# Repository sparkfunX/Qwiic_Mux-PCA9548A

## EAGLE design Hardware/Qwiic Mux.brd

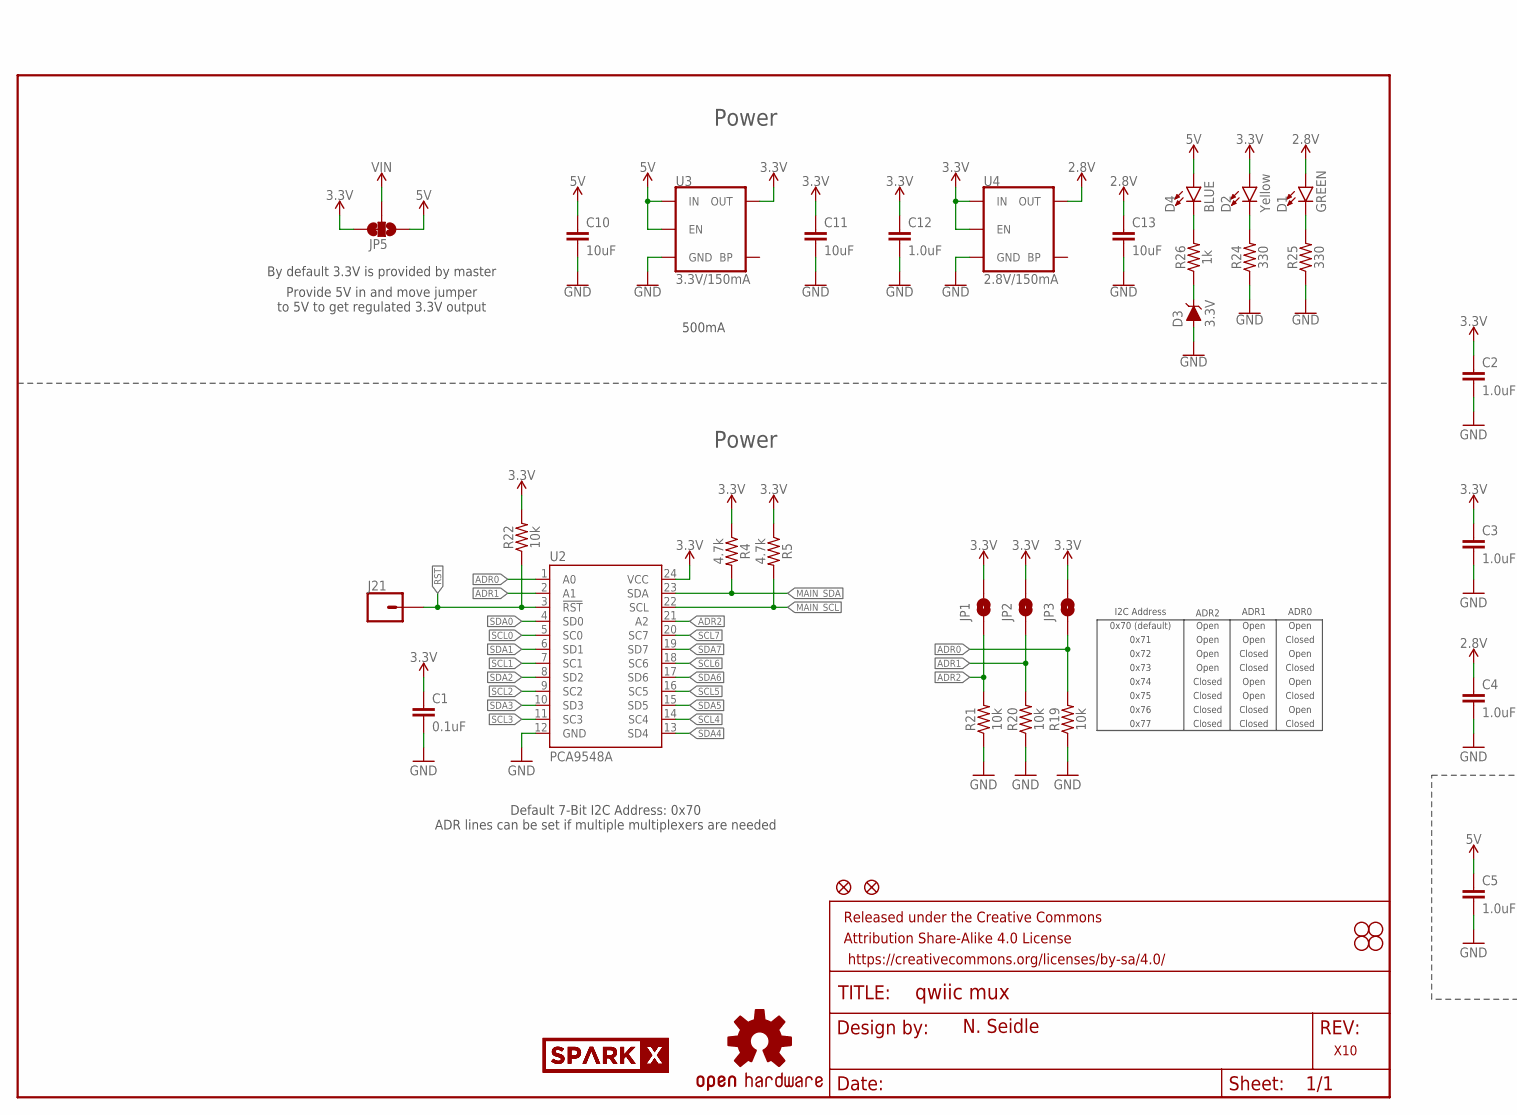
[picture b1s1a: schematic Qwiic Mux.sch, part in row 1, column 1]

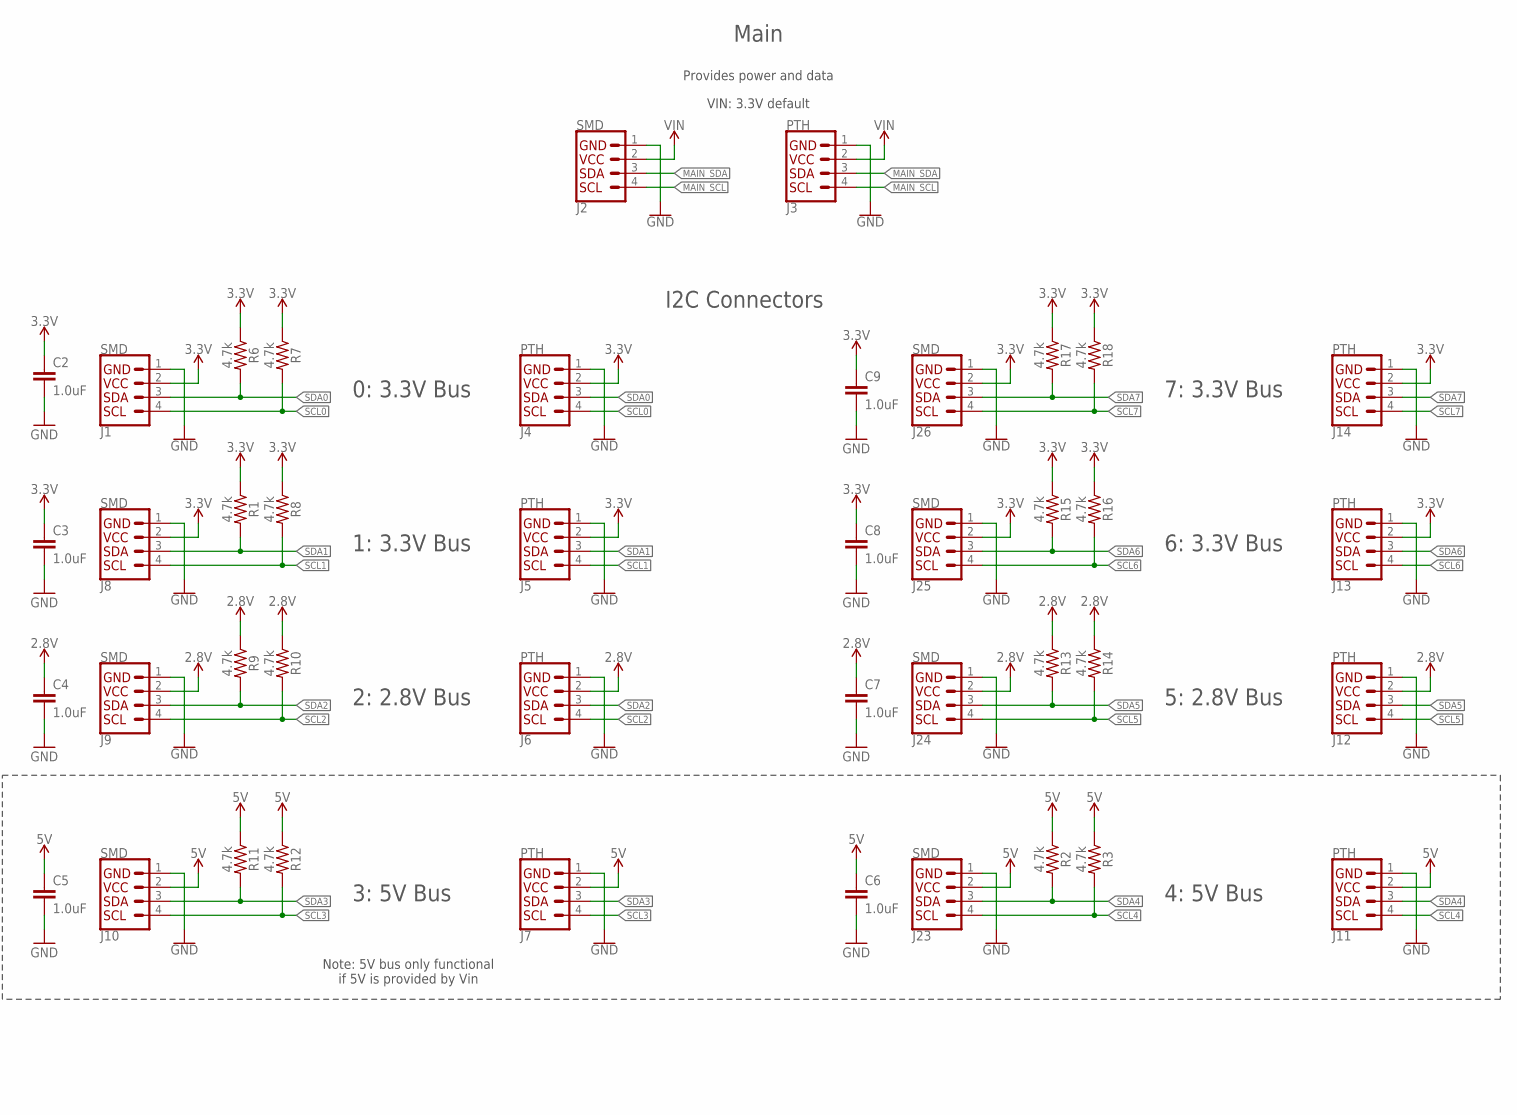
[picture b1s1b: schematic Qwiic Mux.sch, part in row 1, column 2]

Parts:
C1: 0.1uF; 0603
C2, C3, C4, C5, C6, C7, C8, C9, C12: 1.0uF; 0603
C10, C11, C13: 10uF; 0603
D1: GREEN; LED-0603
D2: Yellow; LED-0603
D3: 3.3V; SOD-323
D4: BLUE; LED-0603
FD1, FD2: FIDUCIAL1X2; FIDUCIAL-1X2
FRAME1: FRAME-LETTER; CREATIVE_COMMONS
H1, H2, H3, H4: STAND-OFF
J1, J2, J8, J9, J10, J23, J24, J25, J26: SMD; 1X04_1MM_RA
J3, J4, J5, J6, J7, J11, J12, J13, J14: PTH; 1X04_NO_SILK
J21: CONN_01PTH_NO_SILK_YES_STOP; 1X01_NO_SILK
JP1, JP2, JP3: JUMPER-SMT_2_NO_SILK; SMT-JUMPER_2_NO_SILK
JP5: JUMPER-SMT_3_1-NC_TRACE_SILK; SMT-JUMPER_3_1-NC_TRACE_SILK
LOGO1: OSHW-LOGOMINI; OSHW-LOGO-MINI
R1, R2, R3, R4, R5, R6, R7, R8, R9, R10, R11, R12, R13, R14, R15, R16, R17, R18: 4.7k; 0603
R19, R20, R21, R22: 10k; 0603
R24, R25: 330; 0603
R26: 1k; 0603
U2: PCA9548A; TSSOP28
U3: 3.3V/150mA; SOT23-5
U4: 2.8V/150mA; SOT23-5
U$1: SPARKX-LOGO3; SPARKX-SMALL
U$2: SPARKX-LOGO5; SPARKX-LARGE

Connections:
2.8V: C4.1, C7.1, C13.1, D1.A, J6.2 (VCC), J9.2 (VCC), J12.2 (VCC), J24.2 (VCC), R9.1, R10.1, R13.1, R14.1, U4.5 (OUT)
3.3V: C1.1, C2.1, C3.1, C8.1, C9.1, C11.1, C12.1, D2.A, J1.2 (VCC), J4.2 (VCC), J5.2 (VCC), J8.2 (VCC), J13.2 (VCC), J14.2 (VCC), J25.2 (VCC), J26.2 (VCC), JP1.2, JP2.2, JP3.2, JP5.3, R1.1, R4.1, R5.1, R6.1, R7.1, R8.1, R15.1, R16.1, R17.1, R18.1, R22.2, U2.24 (VCC), U3.5 (OUT), U4.1 (IN), U4.3 (EN)
5V: C5.1, C6.1, C10.1, D4.A, J7.2 (VCC), J10.2 (VCC), J11.2 (VCC), J23.2 (VCC), JP5.1, R2.1, R3.1, R11.1, R12.1, U3.1 (IN), U3.3 (EN)
!RST: J21.1, R22.1, U2.3 (!RST)
ADR0: JP3.1, R19.2, U2.1 (A0)
ADR1: JP2.1, R20.2, U2.2 (A1)
ADR2: JP1.1, R21.2, U2.21 (A2)
GND: C1.2, C2.2, C3.2, C4.2, C5.2, C6.2, C7.2, C8.2, C9.2, C10.2, C11.2, C12.2, C13.2, D3.A, J1.1 (GND), J2.1 (GND), J3.1 (GND), J4.1 (GND), J5.1 (GND), J6.1 (GND), J7.1 (GND), J8.1 (GND), J9.1 (GND), J10.1 (GND), J11.1 (GND), J12.1 (GND), J13.1 (GND), J14.1 (GND), J23.1 (GND), J24.1 (GND), J25.1 (GND), J26.1 (GND), R19.1, R20.1, R21.1, R24.1, R25.1, U2.12 (GND), U3.2 (GND), U4.2 (GND)
MAIN_SCL: J2.4 (SCL), J3.4 (SCL), R5.2, U2.22 (SCL)
MAIN_SDA: J2.3 (SDA), J3.3 (SDA), R4.2, U2.23 (SDA)
unnamed: D2.C, R24.2
unnamed: D3.C, R26.1
unnamed: D1.C, R25.2
unnamed: D4.C, R26.2
SCL0: J1.4 (SCL), J4.4 (SCL), R7.2, U2.5 (SC0)
SCL1: J5.4 (SCL), J8.4 (SCL), R8.2, U2.7 (SC1)
SCL2: J6.4 (SCL), J9.4 (SCL), R10.2, U2.9 (SC2)
SCL3: J7.4 (SCL), J10.4 (SCL), R12.2, U2.11 (SC3)
SCL4: J11.4 (SCL), J23.4 (SCL), R3.2, U2.14 (SC4)
SCL5: J12.4 (SCL), J24.4 (SCL), R14.2, U2.16 (SC5)
SCL6: J13.4 (SCL), J25.4 (SCL), R16.2, U2.18 (SC6)
SCL7: J14.4 (SCL), J26.4 (SCL), R18.2, U2.20 (SC7)
SDA0: J1.3 (SDA), J4.3 (SDA), R6.2, U2.4 (SD0)
SDA1: J5.3 (SDA), J8.3 (SDA), R1.2, U2.6 (SD1)
SDA2: J6.3 (SDA), J9.3 (SDA), R9.2, U2.8 (SD2)
SDA3: J7.3 (SDA), J10.3 (SDA), R11.2, U2.10 (SD3)
SDA4: J11.3 (SDA), J23.3 (SDA), R2.2, U2.13 (SD4)
SDA5: J12.3 (SDA), J24.3 (SDA), R13.2, U2.15 (SD5)
SDA6: J13.3 (SDA), J25.3 (SDA), R15.2, U2.17 (SD6)
SDA7: J14.3 (SDA), J26.3 (SDA), R17.2, U2.19 (SD7)
VIN: J2.2 (VCC), J3.2 (VCC), JP5.2

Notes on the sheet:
N. Seidle
X10
I2C Connectors
Default 7-Bit I2C Address: 0x70 ADR lines can be set if multiple multiplexers are needed
Main
0: 3.3V Bus
1: 3.3V Bus
2: 2.8V Bus
3: 5V Bus
4: 5V Bus
5: 2.8V Bus
6: 3.3V Bus
7: 3.3V Bus
Power
By default 3.3V is provided by master
Provides power and data
Provide 5V in and move jumper to 5V to get regulated 3.3V output
VIN: 3.3V default
Note: 5V bus only functional if 5V is provided by Vin
500mA
I2C Address
ADR0
ADR1
ADR2
Open
Closed
0x70 (default)
0x71
0x72
0x73
0x74
0x75
0x76
0x77

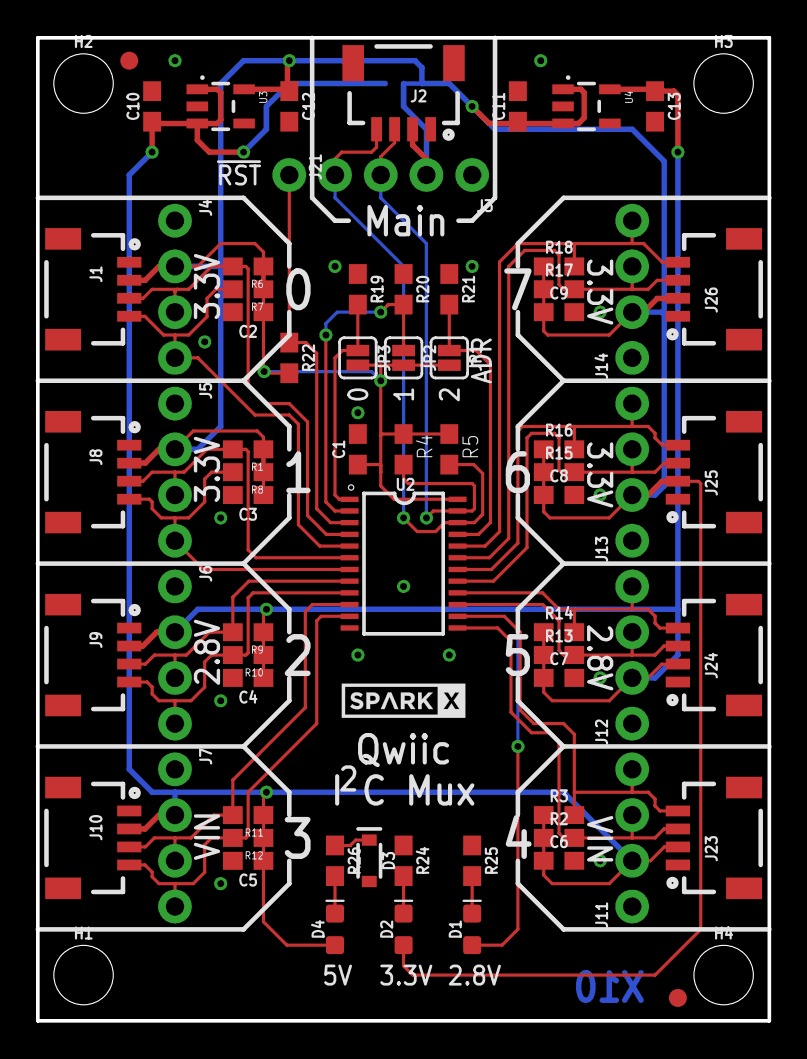
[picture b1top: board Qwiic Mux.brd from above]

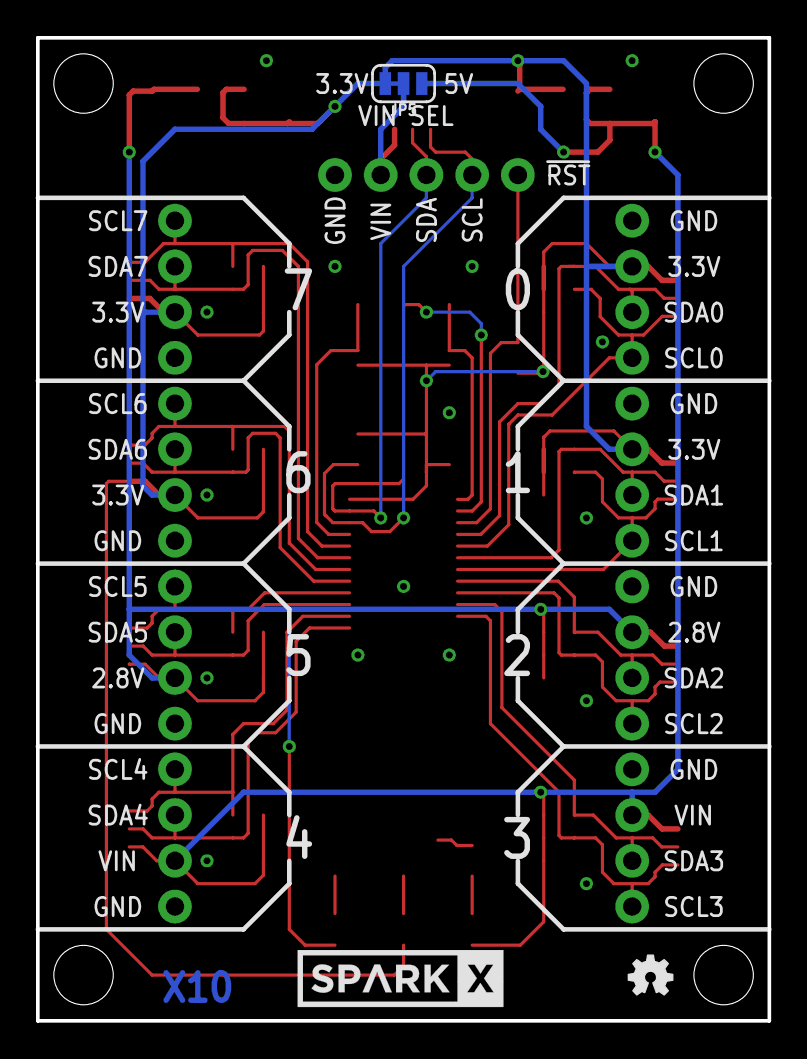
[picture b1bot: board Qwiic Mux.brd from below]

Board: 2 copper layers, 40.6 x 54.6 mm, 78 parts (3 on the bottom side), 31 nets.

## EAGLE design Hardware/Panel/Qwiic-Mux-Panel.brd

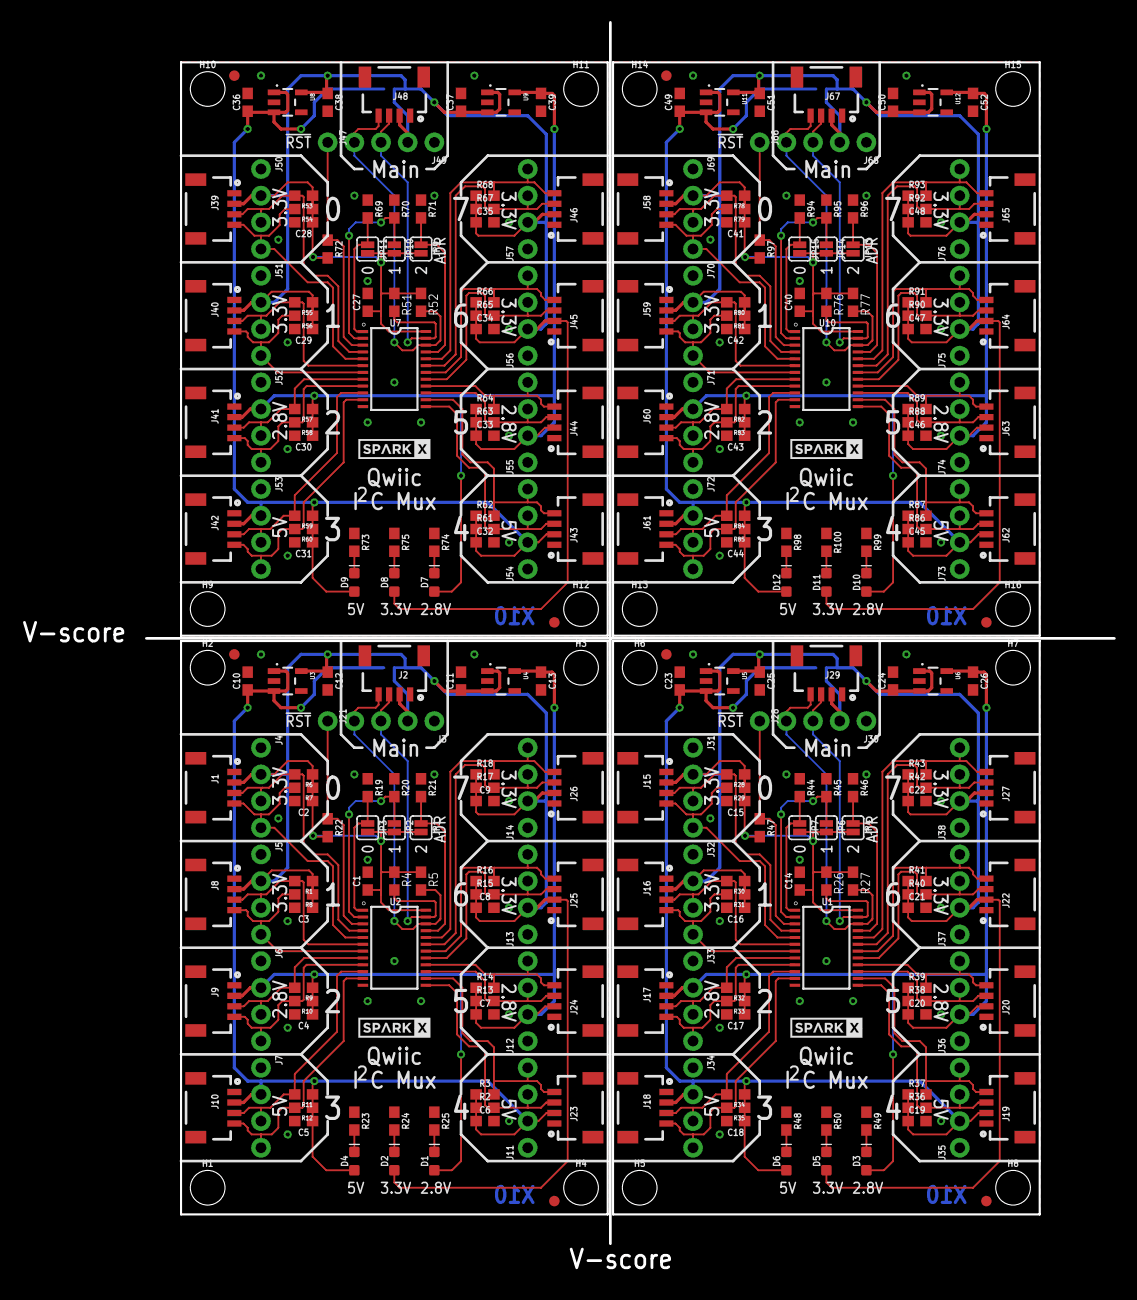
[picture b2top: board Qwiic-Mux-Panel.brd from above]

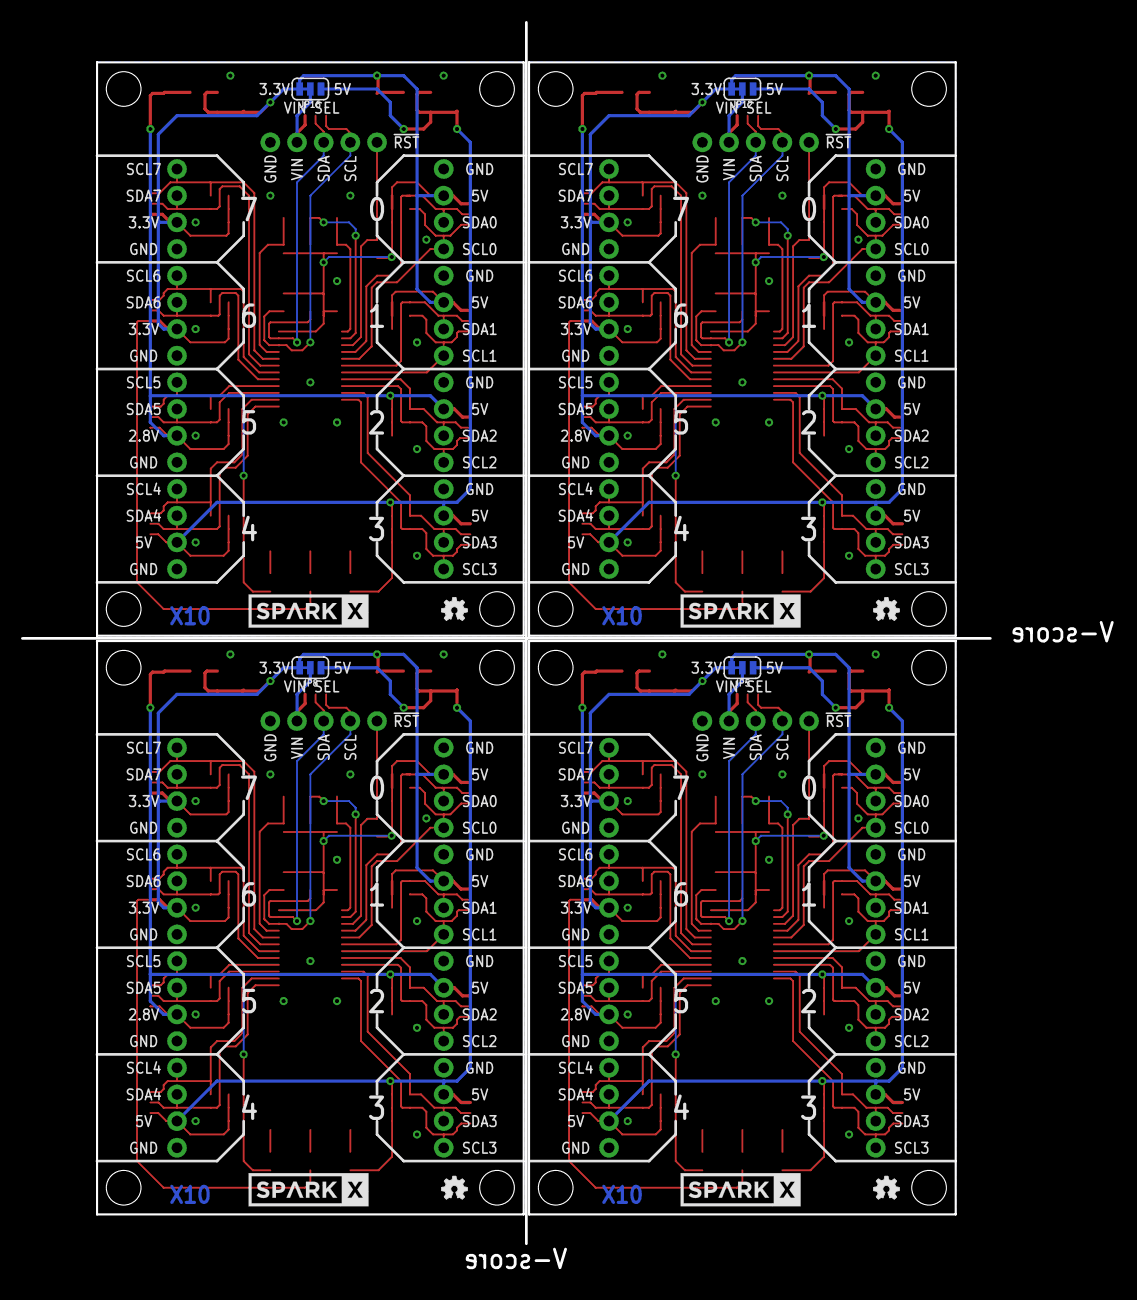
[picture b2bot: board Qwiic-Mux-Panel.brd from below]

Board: 2 copper layers, 104.0 x 119.6 mm, 304 parts (12 on the bottom side), 120 nets.

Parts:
C1, C14, C27, C40: 0.1uF; 0603
C2, C3, C4, C5, C6, C7, C8, C9, C12, C15, C16, C17, C18, C19, C20, C21, C22, C25, C28, C29, C30, C31, C32, C33, C34, C35, C38, C41, C42, C43, C44, C45, C46, C47, C48, C51: 1.0uF; 0603
C10, C11, C13, C23, C24, C26, C36, C37, C39, C49, C50, C52: 10uF; 0603
D1, D3, D7, D10: GREEN; LED-0603
D2, D5, D8, D11: Yellow; LED-0603
D4, D6, D9, D12: BLUE; LED-0603
FD1, FD2, FD3, FD4, FD5, FD6, FD7, FD8: FIDUCIAL1X2; FIDUCIAL-1X2
H1, H2, H3, H4, H5, H6, H7, H8, H9, H10, H11, H12, H13, H14, H15, H16: STAND-OFF
J1, J2, J8, J9, J10, J15, J16, J17, J18, J19, J20, J22, J23, J24, J25, J26, J27, J29, J39, J40, J41, J42, J43, J44, J45, J46, J48, J58, J59, J60, J61, J62, J63, J64, J65, J67: SMD; 1X04_1MM_RA
J3, J4, J5, J6, J7, J11, J12, J13, J14, J30, J31, J32, J33, J34, J35, J36, J37, J38, J49, J50, J51, J52, J53, J54, J55, J56, J57, J68, J69, J70, J71, J72, J73, J74, J75, J76: PTH; 1X04_NO_SILK
J21, J28, J47, J66: 1X01_NO_SILK
JP1, JP2, JP3, JP4, JP6, JP7, JP9, JP10, JP11, JP13, JP14, JP15: SMT-JUMPER_2_NO_SILK
JP5, JP8, JP12, JP16: SMT-JUMPER_3_1-NC_TRACE_SILK
LOGO1, LOGO2, LOGO3, LOGO4: OSHW-LOGOMINI; OSHW-LOGO-MINI
R1, R2, R3, R4, R5, R6, R7, R8, R9, R10, R11, R12, R13, R14, R15, R16, R17, R18, R26, R27, R28, R29, R30, R31, R32, R33, R34, R35, R36, R37, R38, R39, R40, R41, R42, R43, R51, R52, R53, R54, R55, R56, R57, R58, R59, R60, R61, R62, R63, R64, R65, R66, R67, R68, R76, R77, R78, R79, R80, R81, R82, R83, R84, R85, R86, R87, R88, R89, R90, R91, R92, R93: 4.7k; 0603
R19, R20, R21, R22, R44, R45, R46, R47, R69, R70, R71, R72, R94, R95, R96, R97: 10k; 0603
R23, R24, R25, R48, R49, R50, R73, R74, R75, R98, R99, R100: 330; 0603
U1, U2, U7, U10: TCA9548A; TSSOP28
U3, U5, U8, U11: 3.3V/150mA; SOT23-5
U4, U6, U9, U12: 2.8V/150mA; SOT23-5
U$1, U$3, U$5, U$7: SPARKX-LOGO3; SPARKX-SMALL
U$2, U$4, U$6, U$8: SPARKX-LOGO5; SPARKX-LARGE

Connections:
2.8V: C4.1, C7.1, C13.1, D1.A, J6.2, J9.2, J12.2, J24.2, R9.1, R10.1, R13.1, R14.1, U4.5
2.8V1: C17.1, C20.1, C26.1, D3.A, J17.2, J20.2, J33.2, J36.2, R32.1, R33.1, R38.1, R39.1, U6.5
2.8V2: C30.1, C33.1, C39.1, D7.A, J41.2, J44.2, J52.2, J55.2, R57.1, R58.1, R63.1, R64.1, U9.5
2.8V3: C43.1, C46.1, C52.1, D10.A, J60.2, J63.2, J71.2, J74.2, R82.1, R83.1, R88.1, R89.1, U12.5
3.3V: C1.1, C2.1, C3.1, C8.1, C9.1, C11.1, C12.1, D2.A, J1.2, J4.2, J5.2, J8.2, J13.2, J14.2, J25.2, J26.2, JP1.2, JP2.2, JP3.2, JP5.3, R1.1, R4.1, R5.1, R6.1, R7.1, R8.1, R15.1, R16.1, R17.1, R18.1, R22.2, U2.24, U3.5, U4.1, U4.3
3.3V1: C14.1, C15.1, C16.1, C21.1, C22.1, C24.1, C25.1, D5.A, J15.2, J16.2, J22.2, J27.2, J31.2, J32.2, J37.2, J38.2, JP4.2, JP6.2, JP7.2, JP8.3, R26.1, R27.1, R28.1, R29.1, R30.1, R31.1, R40.1, R41.1, R42.1, R43.1, R47.2, U1.24, U5.5, U6.1, U6.3
3.3V2: C27.1, C28.1, C29.1, C34.1, C35.1, C37.1, C38.1, D8.A, J39.2, J40.2, J45.2, J46.2, J50.2, J51.2, J56.2, J57.2, JP9.2, JP10.2, JP11.2, JP12.3, R51.1, R52.1, R53.1, R54.1, R55.1, R56.1, R65.1, R66.1, R67.1, R68.1, R72.2, U7.24, U8.5, U9.1, U9.3
3.3V3: C40.1, C41.1, C42.1, C47.1, C48.1, C50.1, C51.1, D11.A, J58.2, J59.2, J64.2, J65.2, J69.2, J70.2, J75.2, J76.2, JP13.2, JP14.2, JP15.2, JP16.3, R76.1, R77.1, R78.1, R79.1, R80.1, R81.1, R90.1, R91.1, R92.1, R93.1, R97.2, U10.24, U11.5, U12.1, U12.3
5V: C5.1, C6.1, C10.1, D4.A, J7.2, J10.2, J11.2, J23.2, JP5.1, R2.1, R3.1, R11.1, R12.1, U3.1, U3.3
5V1: C18.1, C19.1, C23.1, D6.A, J18.2, J19.2, J34.2, J35.2, JP8.1, R34.1, R35.1, R36.1, R37.1, U5.1, U5.3
5V2: C31.1, C32.1, C36.1, D9.A, J42.2, J43.2, J53.2, J54.2, JP12.1, R59.1, R60.1, R61.1, R62.1, U8.1, U8.3
5V3: C44.1, C45.1, C49.1, D12.A, J61.2, J62.2, J72.2, J73.2, JP16.1, R84.1, R85.1, R86.1, R87.1, U11.1, U11.3
!RST: J21.1, R22.1, U2.3
!RST1: J28.1, R47.1, U1.3
!RST2: J47.1, R72.1, U7.3
!RST3: J66.1, R97.1, U10.3
ADR0: JP3.1, R19.2, U2.1
ADR1: JP2.1, R20.2, U2.2
ADR2: JP1.1, R21.2, U2.21
ADR3: JP6.1, R45.2, U1.2
ADR4: JP7.1, R44.2, U1.1
ADR5: JP4.1, R46.2, U1.21
ADR6: JP10.1, R70.2, U7.2
ADR7: JP11.1, R69.2, U7.1
ADR8: JP9.1, R71.2, U7.21
ADR9: JP14.1, R95.2, U10.2
ADR10: JP15.1, R94.2, U10.1
ADR11: JP13.1, R96.2, U10.21
GND: C1.2, C2.2, C3.2, C4.2, C5.2, C6.2, C7.2, C8.2, C9.2, C10.2, C11.2, C12.2, C13.2, J1.1, J2.1, J3.1, J4.1, J5.1, J6.1, J7.1, J8.1, J9.1, J10.1, J11.1, J12.1, J13.1, J14.1, J23.1, J24.1, J25.1, J26.1, R19.1, R20.1, R21.1, R23.1, R24.1, R25.1, U2.12, U3.2, U4.2
GND1: C14.2, C15.2, C16.2, C17.2, C18.2, C19.2, C20.2, C21.2, C22.2, C23.2, C24.2, C25.2, C26.2, J15.1, J16.1, J17.1, J18.1, J19.1, J20.1, J22.1, J27.1, J29.1, J30.1, J31.1, J32.1, J33.1, J34.1, J35.1, J36.1, J37.1, J38.1, R44.1, R45.1, R46.1, R48.1, R49.1, R50.1, U1.12, U5.2, U6.2
GND2: C27.2, C28.2, C29.2, C30.2, C31.2, C32.2, C33.2, C34.2, C35.2, C36.2, C37.2, C38.2, C39.2, J39.1, J40.1, J41.1, J42.1, J43.1, J44.1, J45.1, J46.1, J48.1, J49.1, J50.1, J51.1, J52.1, J53.1, J54.1, J55.1, J56.1, J57.1, R69.1, R70.1, R71.1, R73.1, R74.1, R75.1, U7.12, U8.2, U9.2
GND3: C40.2, C41.2, C42.2, C43.2, C44.2, C45.2, C46.2, C47.2, C48.2, C49.2, C50.2, C51.2, C52.2, J58.1, J59.1, J60.1, J61.1, J62.1, J63.1, J64.1, J65.1, J67.1, J68.1, J69.1, J70.1, J71.1, J72.1, J73.1, J74.1, J75.1, J76.1, R94.1, R95.1, R96.1, R98.1, R99.1, R100.1, U10.12, U11.2, U12.2
MAIN_SCL: J2.4, J3.4, R5.2, U2.22
MAIN_SCL1: J29.4, J30.4, R27.2, U1.22
MAIN_SCL2: J48.4, J49.4, R52.2, U7.22
MAIN_SCL3: J67.4, J68.4, R77.2, U10.22
MAIN_SDA: J2.3, J3.3, R4.2, U2.23
MAIN_SDA1: J29.3, J30.3, R26.2, U1.23
MAIN_SDA2: J48.3, J49.3, R51.2, U7.23
MAIN_SDA3: J67.3, J68.3, R76.2, U10.23
unnamed: D2.C, R24.2
unnamed: D5.C, R50.2
unnamed: D1.C, R25.2
unnamed: D4.C, R23.2
unnamed: D3.C, R49.2
unnamed: D6.C, R48.2
unnamed: D8.C, R75.2
unnamed: D7.C, R74.2
unnamed: D9.C, R73.2
unnamed: D11.C, R100.2
unnamed: D10.C, R99.2
unnamed: D12.C, R98.2
SCL0: J1.4, J4.4, R7.2, U2.5
SCL1: J5.4, J8.4, R8.2, U2.7
SCL2: J6.4, J9.4, R10.2, U2.9
SCL3: J7.4, J10.4, R12.2, U2.11
SCL4: J11.4, J23.4, R3.2, U2.14
SCL5: J12.4, J24.4, R14.2, U2.16
SCL6: J13.4, J25.4, R16.2, U2.18
SCL7: J14.4, J26.4, R18.2, U2.20
SCL8: J15.4, J31.4, R29.2, U1.5
SCL9: J16.4, J32.4, R31.2, U1.7
SCL10: J18.4, J34.4, R35.2, U1.11
SCL11: J19.4, J35.4, R37.2, U1.14
SCL12: J20.4, J36.4, R39.2, U1.16
SCL13: J22.4, J37.4, R41.2, U1.18
SCL14: J27.4, J38.4, R43.2, U1.20
SCL15: J17.4, J33.4, R33.2, U1.9
SCL16: J39.4, J50.4, R54.2, U7.5
SCL17: J40.4, J51.4, R56.2, U7.7
SCL18: J42.4, J53.4, R60.2, U7.11
SCL19: J43.4, J54.4, R62.2, U7.14
SCL20: J44.4, J55.4, R64.2, U7.16
SCL21: J45.4, J56.4, R66.2, U7.18
SCL22: J46.4, J57.4, R68.2, U7.20
SCL23: J41.4, J52.4, R58.2, U7.9
SCL24: J58.4, J69.4, R79.2, U10.5
SCL25: J59.4, J70.4, R81.2, U10.7
SCL26: J61.4, J72.4, R85.2, U10.11
SCL27: J62.4, J73.4, R87.2, U10.14
SCL28: J63.4, J74.4, R89.2, U10.16
SCL29: J64.4, J75.4, R91.2, U10.18
SCL30: J65.4, J76.4, R93.2, U10.20
SCL31: J60.4, J71.4, R83.2, U10.9
SDA0: J1.3, J4.3, R6.2, U2.4
SDA1: J5.3, J8.3, R1.2, U2.6
SDA2: J6.3, J9.3, R9.2, U2.8
SDA3: J7.3, J10.3, R11.2, U2.10
SDA4: J11.3, J23.3, R2.2, U2.13
SDA5: J12.3, J24.3, R13.2, U2.15
SDA6: J13.3, J25.3, R15.2, U2.17
SDA7: J14.3, J26.3, R17.2, U2.19
SDA8: J15.3, J31.3, R28.2, U1.4
SDA9: J16.3, J32.3, R30.2, U1.6
SDA10: J18.3, J34.3, R34.2, U1.10
SDA11: J19.3, J35.3, R36.2, U1.13
SDA12: J20.3, J36.3, R38.2, U1.15
SDA13: J27.3, J38.3, R42.2, U1.19
SDA14: J22.3, J37.3, R40.2, U1.17
SDA15: J17.3, J33.3, R32.2, U1.8
SDA16: J39.3, J50.3, R53.2, U7.4
SDA17: J40.3, J51.3, R55.2, U7.6
SDA18: J42.3, J53.3, R59.2, U7.10
SDA19: J43.3, J54.3, R61.2, U7.13
SDA20: J44.3, J55.3, R63.2, U7.15
SDA21: J46.3, J57.3, R67.2, U7.19
SDA22: J45.3, J56.3, R65.2, U7.17
SDA23: J41.3, J52.3, R57.2, U7.8
SDA24: J58.3, J69.3, R78.2, U10.4
SDA25: J59.3, J70.3, R80.2, U10.6
SDA26: J61.3, J72.3, R84.2, U10.10
SDA27: J62.3, J73.3, R86.2, U10.13
SDA28: J63.3, J74.3, R88.2, U10.15
SDA29: J65.3, J76.3, R92.2, U10.19
SDA30: J64.3, J75.3, R90.2, U10.17
SDA31: J60.3, J71.3, R82.2, U10.8
VIN: J2.2, J3.2, JP5.2
VIN1: J29.2, J30.2, JP8.2
VIN2: J48.2, J49.2, JP12.2
VIN3: J67.2, J68.2, JP16.2

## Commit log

2017-04-17 :octocat: Added .gitattributes & .gitignore files
2017-04-18 Fixing silk indicators on bottom. Fixing tented vias on panel.
2017-04-21 Adding example firmware
2017-04-21 Fixing silk. Fixing 5V LED circuit.

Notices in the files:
parts and their libraries:
SparkFun-Aesthetics: Licensing: CC v3.0 Share-Alike You are welcome to use this library for commercial purposes.
SparkFun-Resistors: Licensing: Creative Commons ShareAlike 4.0 International - https://creativecommons.org/licenses/by-sa/4.0
SparkFun-Aesthetics: Released under the Creative Commons
